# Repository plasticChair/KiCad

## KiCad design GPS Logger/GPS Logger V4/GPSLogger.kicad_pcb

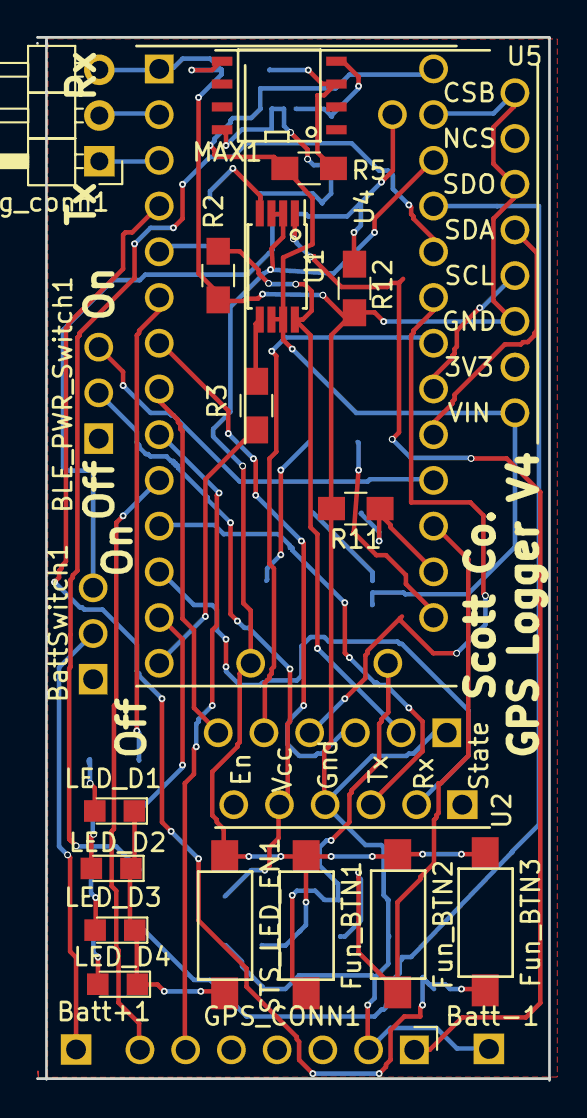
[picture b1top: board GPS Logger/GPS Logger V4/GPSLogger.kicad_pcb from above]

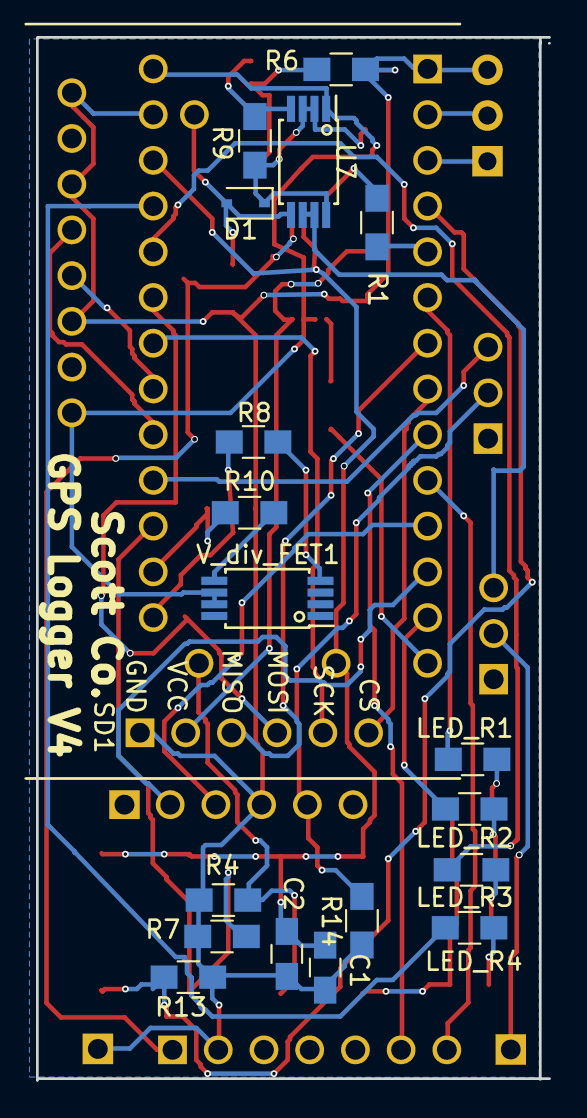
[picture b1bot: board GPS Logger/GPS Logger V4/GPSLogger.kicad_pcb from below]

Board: 2 copper layers, 28.4 x 58.0 mm, 43 parts (19 on the bottom side), 45 nets.

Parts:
BLE_PWR_Switch1: BLE_PWR_Switch; Pin_Header_1x03_Pitch2.54mm
Batt+1: +Batt; Pin_Header_1x01_Pitch2.54mm
Batt-1: -Batt; Pin_Header_1x01_Pitch2.54mm
BattSwitch1: BattSwitch; Pin_Header_1x03_Pitch2.54mm
C1: 82nF; C_0805_HandSoldering
C2: 2.2uF; C_0805_HandSoldering
D1: D; D_SOD-323
Fun_BTN1, Fun_BTN3: LVCutoff_reset; SMD_Switch_3x6
Fun_BTN2: Fun_BTN; SMD_Switch_3x6
GPS_CONN1: GPS Connector; Pin_Header_Angled_1x07_Pitch2.54mm
LED_D1: BLUE; LED_0805
LED_D2: GREEN; LED_0805
LED_D3: RED; LED_0805
LED_D4: ORANGE; LED_0805
LED_R1: 5.6; R_0805_HandSoldering
LED_R2: 10; R_0805_HandSoldering
LED_R3, LED_R4: 56; R_0805_HandSoldering
MAX1: MAX8212; SOIC-8-N
R1, R3, R4, R7, R8, R13: 10k; R_0805_HandSoldering
R2, R5, R12, R14: 100k; R_0805_HandSoldering
R6: 56k; R_0805_HandSoldering
R9: 1M; R_0805_HandSoldering
R10: 82k; R_0805_HandSoldering
R11: 22k; R_0805_HandSoldering
SD1: SDCard_Breakout
STS_LED_EN1: STS_LED_EN; SMD_Switch_3x6
U1, U7: Si6943DQ; TSSOP-8_4.4x3mm_Pitch0.65mm_custom
U2: BLE_module; HM-10_breakout
U4: Teensy-LC; Teensy_LC
U5: GY-91
V_div_FET1: VDiv_FDW254p; TSSOP-8_4.4x3mm_Pitch0.65mm_custom
debug_conn1: debug_conn; Pin_Header_Angled_1x03_Pitch2.54mm

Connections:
+3V3: C1.1, C2.1, Fun_BTN1.2, Fun_BTN2.2, Fun_BTN3.2, STS_LED_EN1.2, U1.2, U1.3, U4.16, U4.31
+BATT: R5.2, U1.6, U1.7, U4.33, U5.1, U7.1, V_div_FET1.6, V_div_FET1.7
/BLE_Pwr_Pin17: BLE_PWR_Switch1.3, U4.24
/BLE_Rx_TX2_10: U2.2, U4.12
/BLE_Tx_RX2_9: U2.3, U4.11
/BattPostSwitch: D1.1, MAX1.8, R9.2, U7.2, U7.3, U7.8
/GPS_Pwr: GPS_CONN1.1, U1.1
/GPS_Rx_TX3_8: GPS_CONN1.7, U4.10
/GPS_Tx_RX3_7: GPS_CONN1.6, U4.9
/LED1_P4: LED_R1.2, U4.6
/LED2_P11: LED_R2.2, U4.13
/LED3_P22: LED_R3.2, U4.29
/LED4_P23: LED_R4.2, U4.30
/SCL: U4.26, U5.4
/SDA: U4.25, U5.5
/SD_En_P12: R3.1, U4.14
/SD_MOSI_P21: SD1.4, U4.28
/SD_SCK_P20: SD1.5, U4.27
/USBPower+: D1.2, R12.2, U4.34, U7.5
GND: Batt-1.1, C1.2, C2.2, GPS_CONN1.2, MAX1.5, R2.2, R4.2, R6.1, R7.2, R11.2, R12.1, R13.2, R14.1, SD1.1, U2.4, U4.1, U4.32, U5.3, U5.6, U5.8, debug_conn1.3
unnamed: BLE_PWR_Switch1.2, R14.2, U2.5
unnamed: Batt+1.1, BattSwitch1.2
unnamed: BattSwitch1.3, U7.6, U7.7
unnamed: Fun_BTN1.1, R4.1, U4.19
unnamed: Fun_BTN2.1, R7.1, U4.23
unnamed: Fun_BTN3.1, R13.1, U4.4
unnamed: LED_D1.1, LED_D2.1, LED_D3.1, LED_D4.1, STS_LED_EN1.1
unnamed: LED_D1.2, LED_R1.1
unnamed: LED_D2.2, LED_R2.1
unnamed: LED_D3.2, LED_R3.1
unnamed: LED_D4.2, LED_R4.1
unnamed: MAX1.3, R5.1, R6.2
unnamed: MAX1.4, R9.1, U7.4
unnamed: R1.1, U1.4
unnamed: R1.2, U4.5
unnamed: R2.1, SD1.2, U1.8
unnamed: R3.2, U1.5
unnamed: R8.1, V_div_FET1.4
unnamed: R8.2, U4.21
unnamed: R10.1, V_div_FET1.5
unnamed: R10.2, R11.1, U4.22
unnamed: SD1.3, U4.7
unnamed: SD1.6, U4.8
unnamed: U4.2, debug_conn1.2
unnamed: U4.3, debug_conn1.1

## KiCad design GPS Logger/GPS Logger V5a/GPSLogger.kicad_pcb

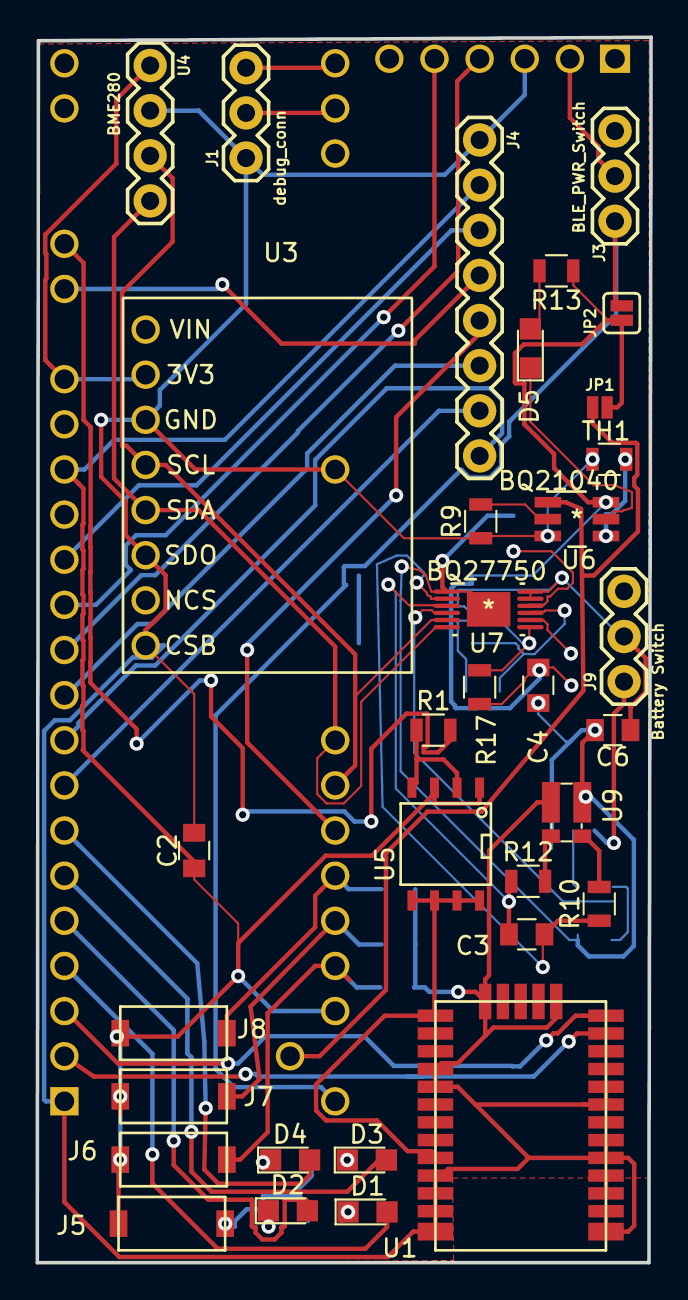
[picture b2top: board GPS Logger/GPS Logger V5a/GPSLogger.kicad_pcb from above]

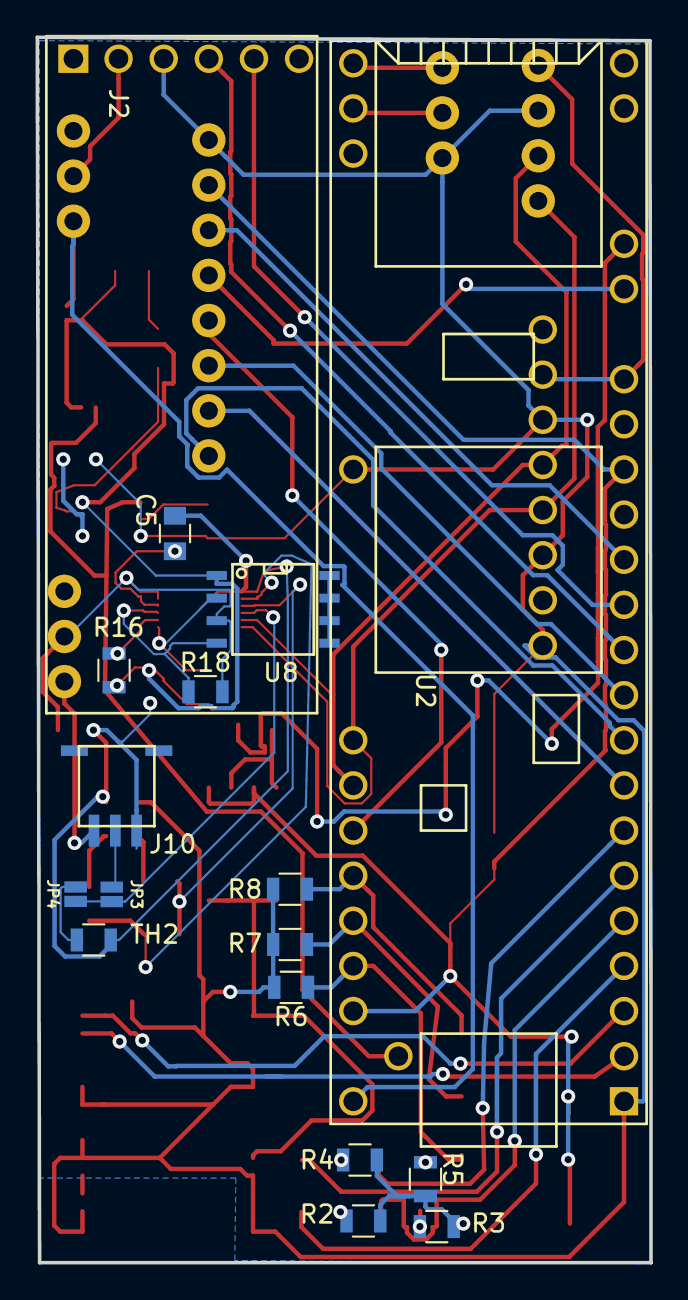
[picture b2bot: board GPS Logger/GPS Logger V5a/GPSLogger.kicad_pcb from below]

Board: 2 copper layers, 34.5 x 69.0 mm, 50 parts (17 on the bottom side), 56 nets.

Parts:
C2, C5: 2.2u; C_0805
C3, C6: 0.1u; C_0805
C4: 1u; C_0805
D1: LED_B; LED_0805
D2: LED_G; LED_0805
D3: LED_R; LED_0805
D4: LED_O; LED_0805
D5: LED; LED_0805
J1: debug_conn; 1X03
J2: BLE_Module; HM-10_breakout
J3: BLE_PWR_Switch; 1X03
J4: Conn_01x08_Male; 1X08
J5: LED_BUTTON; Tact_SMD_Switch
J6: BTN1; Tact_SMD_Switch
J7: BTN2; Tact_SMD_Switch
J8: BTN3; Tact_SMD_Switch
J9: Battery Switch; 1X03
J10: Conn_01x03_Male; molex_78172-0003
JP1, JP3, JP4: Jumper_NO_Small; SMT-JUMPER_2_NO_NO-SILK
JP2: Jumper_NC_Small; SMT-JUMPER_2_NC_PASTE_SILK
R1, R6, R7, R8: 10k; R_0805
R2: 5.6; R_0805
R3, R16: 10; R_0805
R4, R5: 56; R_0805
R9: Riset; R_0805
R10, R12: 100; R_0805
R13: 330; R_0805
R17, R18: 10M; R_0805
TH1, TH2: NTC; R_0805
U1: CAM_M8Q; CAM-M8Q
U2: Teensy3.6; Teensy35_36
U3: GY-91
U4: BME280; 1X04
U5: APM4953; SOIC-8-N
U6: BQ21040
U7: BQ27750
U8: CEM9926A; SOIC-8-N
U9: R_0612; R_Shunt_Vishay_WSKW0612

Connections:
+3V3: C2.1, J4.2, J5.1, J6.2, J7.2, J8.2, U2.15, U2.51, U5.1, U5.3
/BLE_Pwr: J2.2, J3.2
/BLE_Rx_TX2_P10: J2.5, U2.12
/BLE_Tx_RX2_P9: J2.4, U2.11
/Debug_Rx_TX5_P33: J1.3, U2.30
/Debug_Tx_RX5_P34: J1.2, U2.31
/GPS_Rx_TX1_P1: U1.26, U2.3
/GPS_Tx_RX1_P0: U1.25, U2.2
/Screen_BUSY_P7: J4.8, U2.9
/Screen_CS_P20: J4.5, U2.47
/Screen_DC_P8: J4.6, U2.10
/Screen_DIN_P11: J4.3, U2.13
/Screen_RST_P6: J4.7, U2.8
/Screen_SCK_P27: J4.4, U2.19
/Sensor_PWR_P25: U2.17, U3.2, U4.1
BattPwr: J3.1, JP2.1, U2.53
BattRtn: C2.2, J1.1, J2.3, J4.1, R6.2, R7.2, R8.2, R9.1, TH1.2, U1.4, U1.5, U1.10, U1.11, U1.12, U1.13, U1.14, U1.15, U1.18, U1.19, U1.21, U1.22, U1.27, U1.31, U2.1, U2.39, U3.3, U3.6, U3.8, U4.2, U6.3, U9.4
Fun_Btn_1_P23: J6.1, R6.1, U2.50
Fun_Btn_2_P22: J7.1, R7.1, U2.49
Fun_Btn_3_P21: J8.1, R8.1, U2.48
GPS_Pwr: U1.1, U1.9, U5.5, U5.6, U5.7, U5.8
GPS_Pwr_En_P28: R1.2, U2.20
LED1_P2: D1.2, U2.4
LED2_P3: D2.2, U2.5
LED3_P4: D3.2, U2.6
LED4_P5: D4.2, U2.7
unnamed: C3.1, R12.1, U7.3
unnamed: C3.2, R10.1, U7.2
unnamed: C4.1, JP1.2, JP2.2, R13.1, R16.2, R17.2, U6.6, U8.1
unnamed: C4.2, C5.2, C6.2, J10.1, TH2.2, U7.1, U7.13, U9.1
unnamed: C5.1, U7.10
unnamed: C6.1, J9.2, R18.2, U7.11, U7.12, U8.3
unnamed: D1.1, R2.1
unnamed: D2.1, R3.1
unnamed: D3.1, R4.1
unnamed: D4.1, R5.1
unnamed: D5.1, U6.5
unnamed: D5.2, R13.2
unnamed: J5.2, R2.2, R3.2, R4.2, R5.2
unnamed: J10.2, JP3.2
unnamed: J9.1, J10.3
unnamed: JP3.1, JP4.1, U7.4
unnamed: JP4.2, TH2.1
unnamed: R1.1, U5.2, U5.4
unnamed: R9.2, U6.2
unnamed: R10.2, U9.2
unnamed: R12.2, U9.3
unnamed: R16.1, U7.8
unnamed: R17.1, U7.7, U8.2
unnamed: R18.1, U7.9, U8.4
unnamed: TH1.1, U6.4
unnamed: U1.16, U1.17
unnamed: U8.5, U8.6, U8.7, U8.8
SCL: U2.46, U3.4, U4.3, U7.5
SDA: U2.45, U3.5, U4.4, U7.6
USBPwr: JP1.1, U2.54, U6.1

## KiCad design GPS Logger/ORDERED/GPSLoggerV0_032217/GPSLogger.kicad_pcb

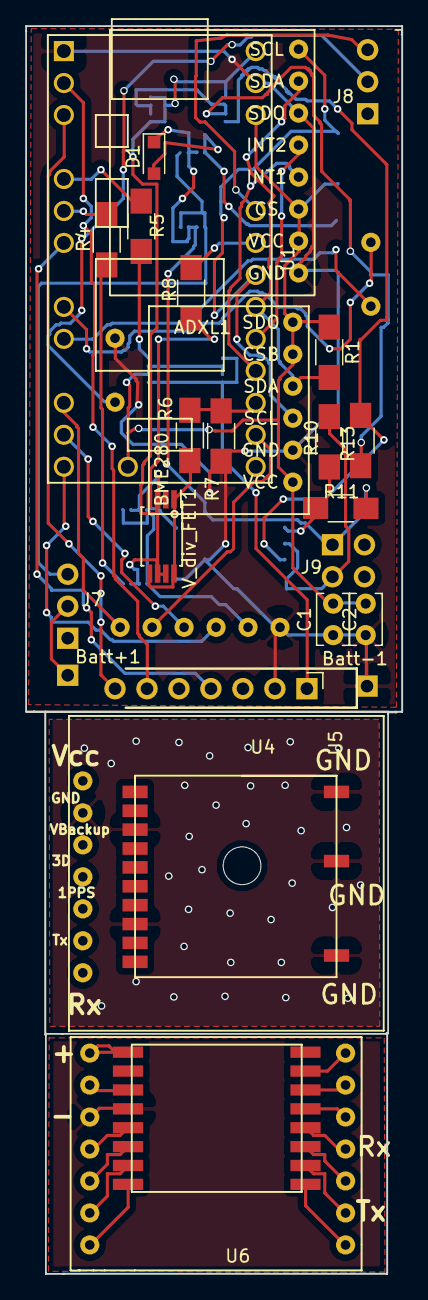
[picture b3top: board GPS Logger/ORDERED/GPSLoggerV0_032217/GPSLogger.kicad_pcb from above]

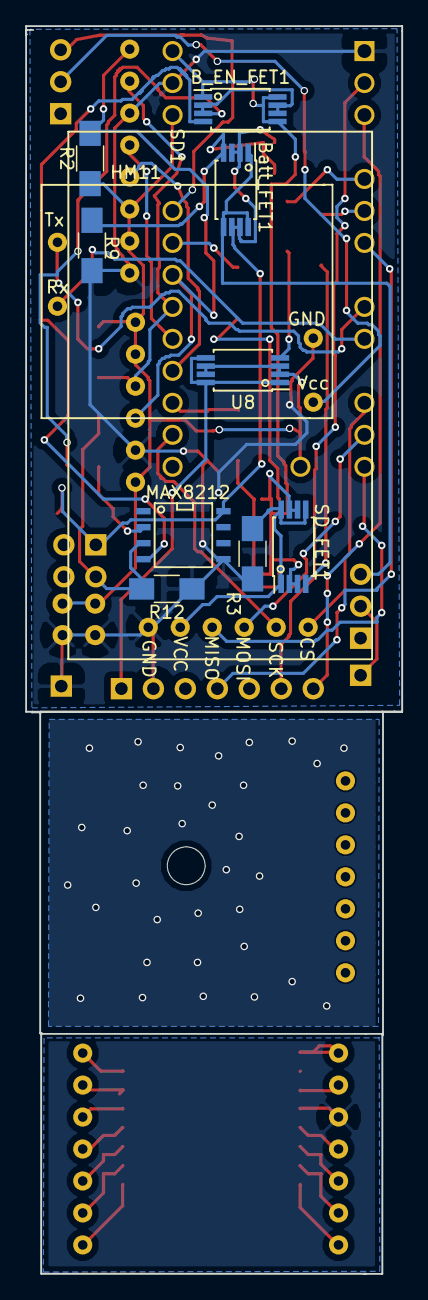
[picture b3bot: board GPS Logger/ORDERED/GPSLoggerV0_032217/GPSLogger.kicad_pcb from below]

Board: 2 copper layers, 29.9 x 99.1 mm, 35 parts (11 on the bottom side), 37 nets.

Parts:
ADXL1: ADXL345_Breakout
BME280: BME280_Breakout
B_EN_FET1: Batt_En_FET; TSSOP-8_4.4x3mm_Pitch0.65mm_custom
Batt+1: +Batt; Pin_Header_1x01_Pitch2.54mm
Batt-1: -Batt; Pin_Header_1x01_Pitch2.54mm
Batt_FET1: Batt_EnFDW254p; TSSOP-8_4.4x3mm_Pitch0.65mm_custom
C1, C2: C; C_Rect_L4.0mm_W2.5mm_P2.50mm
D1: D_Schottky; D_SOD-323_HandSoldering
HM11: HM-11_BreakConns
J7: BattSwitch; Pin_Header_1x03_Pitch2.54mm
J8: HM11Switch; Pin_Header_1x03_Pitch2.54mm
J9: CONN_02X02; Pin_Header_Angled_2x02_Pitch2.54mm
MAX8212: MAX8212; SOIC-8-N
R1, R2, R6, R7: R; R_1206_HandSoldering
R3, R4, R5: R_Small; R_1206_HandSoldering
R8: 10k; R_1206_HandSoldering
R9: 100k; R_1206_HandSoldering
R10, R11, R12, R13: 1M; R_1206_HandSoldering
SD1: SDCard_Breakout
SD_FET1: SD_EN_FDW254p; TSSOP-8_4.4x3mm_Pitch0.65mm_custom
U1: Teensy-LC; Teensy_LC
U4: GNS601_Breakout
U5: GPS Connector; Pin_Header_Angled_1x07_Pitch2.54mm
U6: HM-11; HM-11_Breakout
U8: GPS_FDW254p; TSSOP-8_4.4x3mm_Pitch0.65mm_custom
V_div_FET1: VDiv_FDW254p; TSSOP-8_4.4x3mm_Pitch0.65mm_custom

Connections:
+3V3: ADXL1.2, ADXL1.3, BME280.1, BME280.2, BME280.6, C1.1, C2.1, R1.1, R2.1, U1.16, U1.31, U8.2
+BATT: B_EN_FET1.1, SD_FET1.2, U1.33, V_div_FET1.2
GND: ADXL1.1, ADXL1.6, BME280.5, Batt-1.1, C1.2, C2.2, HM11.12, MAX8212.5, R3.2, R7.2, R9.1, R12.1, SD1.1, U1.1, U5.2
unnamed: ADXL1.4, U1.23
unnamed: ADXL1.5, U1.24
unnamed: ADXL1.7, BME280.3, R1.2, U1.25
unnamed: ADXL1.8, BME280.4, R2.2, U1.26
unnamed: B_EN_FET1.2, R13.2
unnamed: B_EN_FET1.4, MAX8212.4, R13.1
unnamed: Batt_FET1.2, D1.1, J9.1, MAX8212.8, R11.2
unnamed: Batt+1.1, J7.2
unnamed: Batt_FET1.1, J7.3
unnamed: Batt_FET1.4, D1.2, R9.2
unnamed: HM11.2, U1.9
unnamed: HM11.4, U1.10
unnamed: HM11.9, J8.2
unnamed: J8.3, U1.28
unnamed: J9.3, MAX8212.3, R10.1, R12.2
unnamed: MAX8212.2, R10.2, R11.1
unnamed: R3.1, SD1.2, SD_FET1.1
unnamed: R4.1, SD_FET1.4
unnamed: R4.2, U1.6
unnamed: R5.1, U8.4
unnamed: R5.2, U1.5
unnamed: R6.1, R7.1, U1.22
unnamed: R6.2, V_div_FET1.1
unnamed: R8.1, V_div_FET1.4
unnamed: R8.2, U1.27
unnamed: SD1.3, U1.14
unnamed: SD1.4, U1.13
unnamed: SD1.5, U1.21
unnamed: SD1.6, U1.12
unnamed: U1.2, U5.6
unnamed: U1.3, U5.7
unnamed: U1.7, U5.4
unnamed: U4.3, U4.8, U4.11, U4.12, U4.13
unnamed: U5.1, U8.1

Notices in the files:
parts and their libraries:
Copyright 2016 Accelerated Designs. All rights reserved.
